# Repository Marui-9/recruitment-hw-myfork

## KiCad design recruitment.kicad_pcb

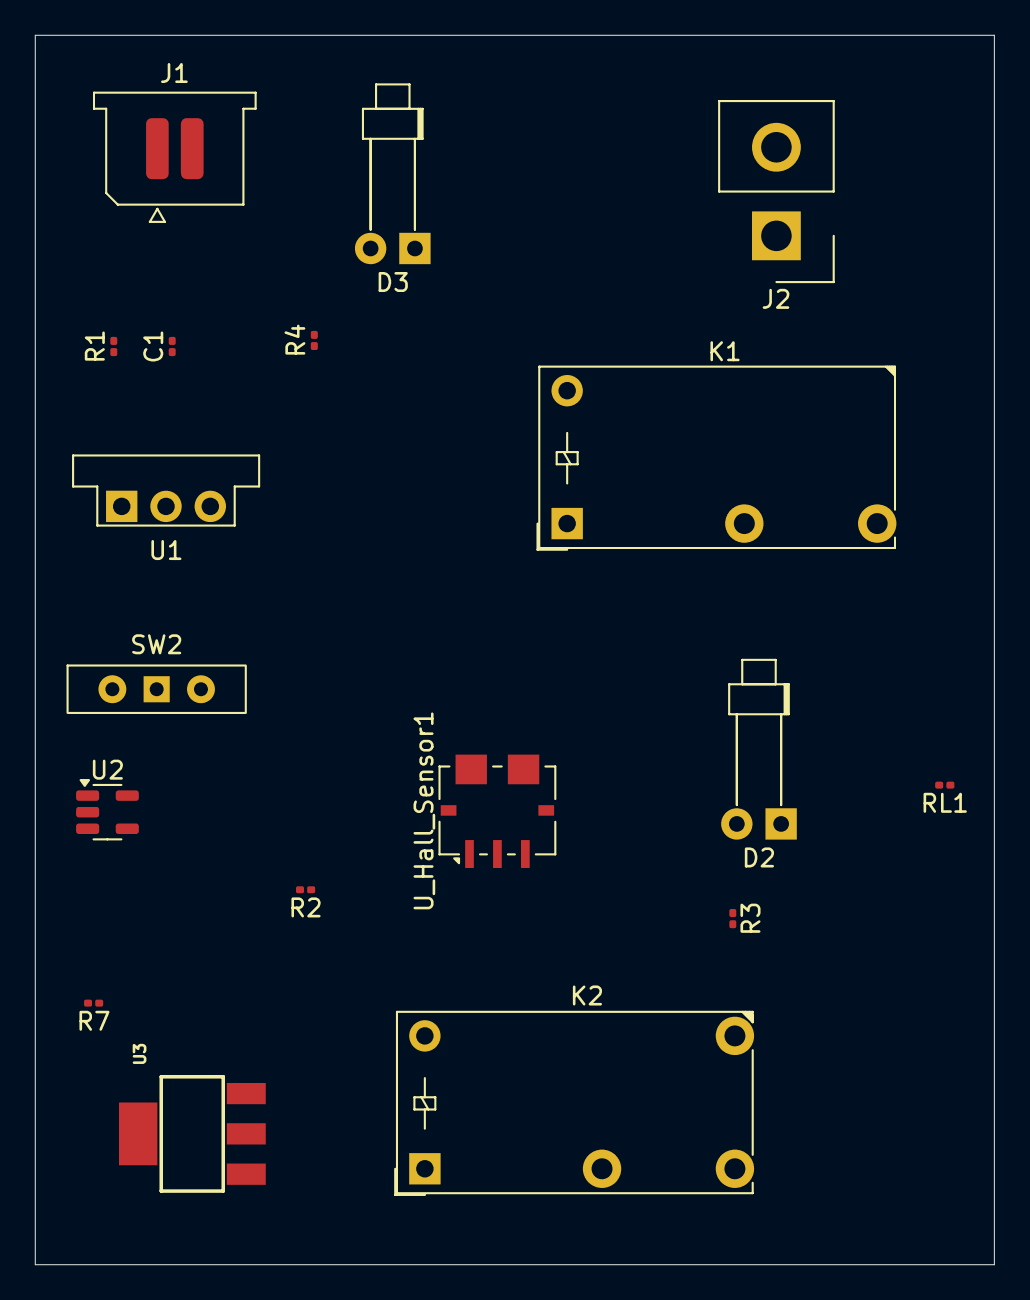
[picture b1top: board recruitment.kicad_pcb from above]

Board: 2 copper layers, 55.0 x 70.5 mm, 18 parts (0 on the bottom side), 13 nets, no tracks yet.

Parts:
C1: 10u; C_0201_0603Metric
D2, D3: LED; LED_D1.8mm_W1.8mm_H2.4mm_Horizontal_O6.35mm_Z4.9mm
J1: Conn_01x02_Pin; Samtec_UMPS-02-XX.X-X-V-S_1x02_P2.0mm_Socket
J2: Conn_01x02_Pin; Samtec_HPM-02-01-x-S_Straight_1x02_Pitch5.08mm
K1: Relay_SPST-NO; Relay_SPST_Finder_32.21-x300
K2: Relay_SPDT; Relay_SPDT_Finder_32.21-x000
R1: 1K; R_0201_0603Metric
R2: 50; R_0201_0603Metric
R3: 2.3K; R_0201_0603Metric
R4: 140; R_0201_0603Metric
R7: 80; R_0201_0603Metric
RL1: R; R_0201_0603Metric
SW2: SW_Wuerth_450301014042; SW_Slide-03_Wuerth-WS-SLTV_10x2.5x6.4_P2.54mm
U1: OKI-78SR-5_1.5-W36-C; Converter_DCDC_Murata_OKI-78SR_Vertical
U2: LM397; SOT-23-5
U3: SCR; SOT223
U_Hall_Sensor1: ACS780LLRTR-050B-T; Allegro_PSOF-7_4.8x6.4mm_P1.60mm

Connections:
/5V: K2.12, R2.2, R4.2, R7.1, SW2.1 (B), SW2.2 (C), U1.3 (OUT), U2.5 (V+), U3.2, U3.4
/36V: J2.1, K1.14, R3.2, RL1.1, U_Hall_Sensor1.5 (IP+)
/A1_m: K1.A1, K2.11
/Monitor/556m: R7.2, U2.3 (+)
/SENS: U2.1 (-), U_Hall_Sensor1.3 (VOUT)
/VCC: R2.1, U_Hall_Sensor1.1 (VCC)
GND: C1.2, D2.1 (K), D3.1 (K), J1.2, J2.2, K1.A2, K2.A2, RL1.2, U1.2 (GND), U2.2 (V-), U_Hall_Sensor1.2 (GND), U_Hall_Sensor1.6 (IP-)
unnamed: C1.1, R1.2
unnamed: D2.2 (A), R3.1
unnamed: D3.2 (A), R4.1
unnamed: J1.1, R1.1, U1.1 (IN)
unnamed: K2.A1, U3.1
unnamed: U2.4, U3.3

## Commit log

2025-03-11 test commit
2025-03-11 added components and hierarchical sheets
2025-03-11 added hierarchical labels to booster schematic
2025-03-12 partial wiring and monitor draft
2025-03-12 monitor changes
2025-03-12 added comparator, to be wired
2025-03-12 monitor internals: temporary solution
2025-03-12 corrected monitor source
2025-03-13 added LPF and correct load LED
2025-03-14 calculated resistances and corrected LPF
2025-03-14 added scr instead of button
2025-03-14 comparator wirirng
2025-03-14 added 36V threshold (fixed)
2025-03-14 added footprints
2025-03-14 wired pcb
